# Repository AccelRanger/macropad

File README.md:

# Macropad

Custom macropad with a custom PCB and firmware.

## How it works

The firmware running on the **ESP32-C6-1M** sends button-number data to the software running on the computer.

The computer-side software processes the received data and emulates keyboard input based on the presets configured on the computer.

## Hardware

- **Microcontroller:** ESP32-C6-1M
- **Button layout:** 3 rows × 3 columns
- **Total buttons:** 9
- **PCB:** Custom-designed PCB

## Planned features

- Bash commands

## Signal flow

1. A button is pressed on the macropad.
2. The ESP32 firmware identifies the button and sends its number to the computer.
3. The computer-side software receives the signal.
4. The software checks the active preset for that button's binding.
5. The software sends the configured keyboard input.

## Project status

This document describes the intended design and features. Firmware and computer-side software is almost done.

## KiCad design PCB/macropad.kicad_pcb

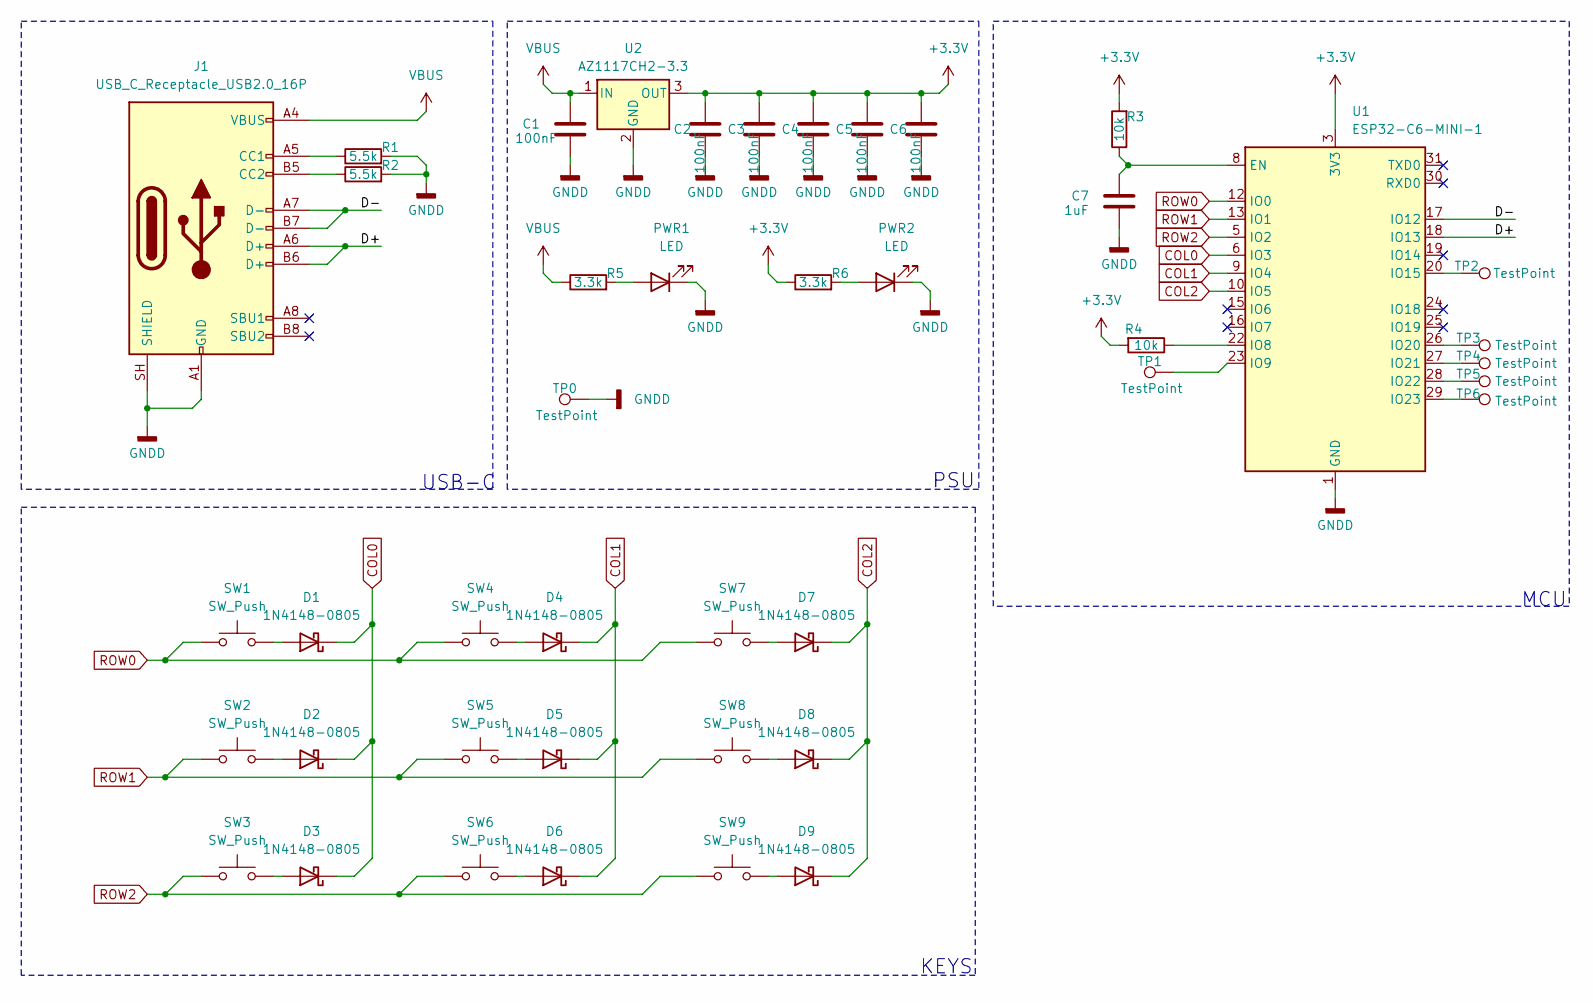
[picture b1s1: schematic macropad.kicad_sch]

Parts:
C1, C2, C3, C4, C5, C6: 100nF; C_0603_1608Metric_Pad1.08x0.95mm_HandSolder
C7: 1uF; C_0603_1608Metric_Pad1.08x0.95mm_HandSolder
D1, D2, D3, D4, D5, D6, D7, D8, D9: 1N4148-0805; D_SOD-323_HandSoldering
J1: USB_C_Receptacle_USB2.0_16P; USB_C_Receptacle_GCT_USB4105-xx-A_16P_TopMnt_Horizontal
PWR1, PWR2: LED; D_0805_2012Metric_Pad1.15x1.40mm_HandSolder
R1, R2: 5.5k; R_0603_1608Metric_Pad0.98x0.95mm_HandSolder
R3, R4: 10k; R_0603_1608Metric_Pad0.98x0.95mm_HandSolder
R5, R6: 3.3k; R_0805_2012Metric_Pad1.20x1.40mm_HandSolder
SW1, SW2, SW3, SW4, SW5, SW6, SW7, SW8, SW9: SW_Push; SW_Cherry_MX_1.00u_PCB
TP0, TP1, TP2, TP3, TP4, TP5, TP6: TestPoint; TestPoint_Pad_D2.0mm
U1: ESP32-C6-MINI-1
U2: AZ1117CH2-3.3; SOT-223-3_TabPin2

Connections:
+3.3V: C2.1, C3.1, C4.1, C5.1, C6.1, R3.2, R4.2, R6.1, U1.3 (3V3), U2.3 (OUT)
/D+: J1.A6 (D+), J1.B6 (D+), U1.18 (IO13)
/D-: J1.A7 (D-), J1.B7 (D-), U1.17 (IO12)
COL0: D1.1 (K), D2.1 (K), D3.1 (K), U1.6 (IO3)
COL1: D4.1 (K), D5.1 (K), D6.1 (K), U1.9 (IO4)
COL2: D7.1 (K), D8.1 (K), D9.1 (K), U1.10 (IO5)
GNDD: C1.2, C2.2, C3.2, C4.2, C5.2, C6.2, C7.2, J1.A1 (GND), J1.A12 (GND), J1.B1 (GND), J1.B12 (GND), J1.SH (SHIELD), PWR1.1 (K), PWR2.1 (K), R1.2, R2.2, TP0.1 (1_1), U1.1 (GND), U1.2 (GND), U1.11 (GND), U1.14 (GND), U1.36 (GND), U1.37 (GND), U1.38 (GND), U1.39 (GND), U1.40 (GND), U1.41 (GND), U1.42 (GND), U1.43 (GND), U1.44 (GND), U1.45 (GND), U1.46 (GND), U1.47 (GND), U1.48 (GND), U1.49 (GND), U1.50 (GND), U1.51 (GND), U1.52 (GND), U1.53 (GND), U2.2 (GND)
unnamed: D1.2 (A), SW1.2
unnamed: D2.2 (A), SW2.2
unnamed: D3.2 (A), SW3.2
unnamed: D4.2 (A), SW4.2
unnamed: D5.2 (A), SW5.2
unnamed: D6.2 (A), SW6.2
unnamed: D7.2 (A), SW7.2
unnamed: D8.2 (A), SW8.2
unnamed: D9.2 (A), SW9.2
unnamed: J1.A5 (CC1), R1.1
unnamed: J1.B5 (CC2), R2.1
unnamed: PWR1.2 (A), R5.2
unnamed: PWR2.2 (A), R6.2
unnamed: C7.1, R3.1, U1.8 (EN)
unnamed: R4.1, U1.22 (IO8)
unnamed: TP1.1 (1_1), U1.23 (IO9)
unnamed: TP2.1 (1_1), U1.20 (IO15)
unnamed: TP3.1 (1_1), U1.26 (IO20)
unnamed: TP4.1 (1_1), U1.27 (IO21)
unnamed: TP5.1 (1_1), U1.28 (IO22)
unnamed: TP6.1 (1_1), U1.29 (IO23)
ROW0: SW1.1, SW4.1, SW7.1, U1.12 (IO0)
ROW1: SW2.1, SW5.1, SW8.1, U1.13 (IO1)
ROW2: SW3.1, SW6.1, SW9.1, U1.5 (IO2)
VBUS: C1.1, J1.A4 (VBUS), J1.A9 (VBUS), J1.B4 (VBUS), J1.B9 (VBUS), R5.1, U2.1 (IN)

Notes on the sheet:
USB-C
KEYS
PSU
MCU

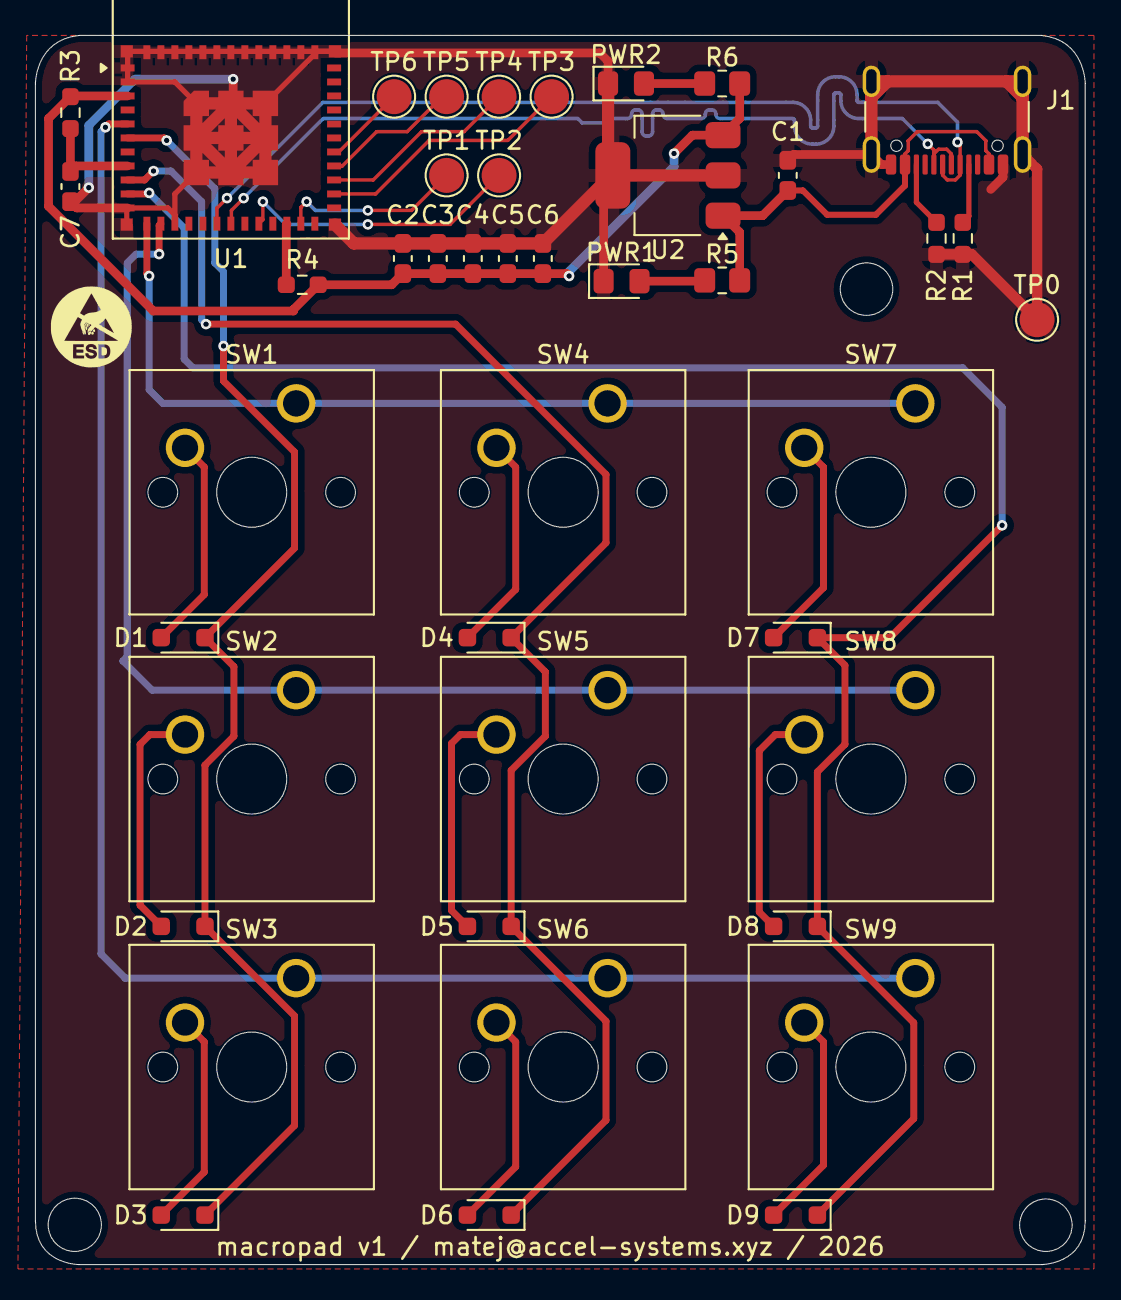
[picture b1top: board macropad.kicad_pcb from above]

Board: 2 copper layers, 60.0 x 70.2 mm, 43 parts (0 on the bottom side), 32 nets.
